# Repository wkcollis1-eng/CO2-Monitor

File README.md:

<div align="center">

# CO2 Monitor

**NDIR CO2 Sensing for Two Rooms, Built to Fail Visibly**

</div>

Two CO2 nodes, one in a bedroom and one in a family room. Each pairs an **Adafruit
SCD30** (PID 4867, a Sensirion NDIR sensor) with a **Seeed XIAO ESP32-C3** on a
small carrier board, inside a **Hammond 1551V4** enclosure. They run **ESPHome**
and report to **Home Assistant**. The bedroom node is built and running; the
family-room node is not built yet.

All behaviour lives in one file, [`esphome/co2-node-common.yaml`](esphome/co2-node-common.yaml).
Each node file holds nothing but its name and its own API key.

*The bedroom node as built: closed on 2026-11-01, and open on 2026-10-27, just
after its USB flash to firmware 1.1 [M: photo EXIF]. More photos are under
[As built](#as-built), and the first five nights of data are under
[Field results](#field-results-the-first-five-nights).*

---

## The problem this is built for

> It is 03:00 in a closed bedroom. The SCD30's cable worked loose an hour ago.
> Nobody is awake to notice, and nobody is coming to fix it tonight.

A CO2 sensor that has stopped answering is dangerous in one specific way: Home
Assistant keeps showing the last good number, and a flat, healthy-looking reading
is exactly what a dead sensor looks like. The acceptance test is **what the node
reports at that moment**, not whether it is online. The firmware is built around
three such moments, named in the header of the common file:

1. **Every boot.** ESPHome 2026.9.1 turns the SCD30's automatic self-calibration
   (ASC) **on** by default and writes that setting to the sensor at every boot
   [S: ESPHome 2026.9.1 source, `scd30/sensor.py:65`, `scd30/scd30.cpp:91`]. ASC
   assumes the sensor regularly sees fresh outdoor air. A closed room in a house
   with no HRV or ERV never does, so ASC would walk the baseline upward where
   nobody would see it. It is turned off explicitly.
2. **Power-up.** The SCD30's first reading after power-up is 0 ppm
   [S: `docs/adafruit-scd30.pdf` p10, p16], and ESPHome passes it through. A
   filter drops it. 0 ppm is not a possible indoor value, so dropping every 0
   costs nothing.
3. **The sensor stops answering.** After 240 s with no reading, the CO2 entity
   goes **unknown** and **CO2 Sensor Fault** turns on. After 900 s the node
   reboots to re-run the sensor setup, **at most three times in a row**. The
   counter survives the reboot, so a dead cable cannot turn into a reboot loop that
   hides it. After the third reboot the node stays up and keeps reporting the fault.
   (1.4: CO2 (2 s) goes unknown at 240 s; CO2, the 1-minute mean, and the SCD30
   temperature and humidity follow at the end of their minute, by 330 s.)

## Status

| | |
|---|---|
| Firmware | **Rev 1.4-draft**, 2026-10-27 (1.0-draft 2026-10-18). On the bedroom node since 2026-10-27 18:13 |
| Compile | Bedroom node, firmware 1.4: compiled on **ESPHome 2026.10.0** with 0 compiler warnings and 0 errors [M: build log, 2026-10-27; config_hash `0x664528e8`]; a deliberately broken lambda fails the same build, so the compile gate can fail. 1.0: both nodes on ESPHome 2026.9.1, 0 warnings, 0 errors [M: build logs, 2026-10-18; config_hash `0xa7e479a5` bedroom, `0xc9ec59d4` family room]. ESPHome's own advisory that an OTA password costs about 3.5 KB of flash prints for both, and is accepted |
| Watchdog | Host-simulated: the clean config passes all 224 checks, and each of the 11 injected faults is caught [M: `harness/faults.py`, 2026-10-27, firmware 1.4; 35 checks and 5 faults on 2026-10-18]. See [The watchdog harness](#the-watchdog-harness) for what that does and does not prove. On the device: SCD30 unplugged on 2026-10-27, firmware 1.1. The node logged the fault at 259 s, HA showed CO2 unknown and the fault on, and the LED strobed [M]. Not repeated on 1.4. The 900 s recovery reboot, and the strobe stopping at the next good reading, have not been seen on the device |
| Deployment | Bedroom node: in Home Assistant since 2026-10-27, firmware 1.4 [M: config_hash `0x664528e8`, ESPHome 2026.10.0, 0 warnings]. On a dresser about 10 ft from the bed [Bill]; 111.65 h with no reset to 2026-11-01 [M]. Family-room node: not built |
| Hardware | **No new PCB.** The carrier is an existing ESP32-C3 sensor-node board. The KiCad file here is that board, unchanged, with the SCD30 and the enclosure placed on it for a 3D fit check |

## Field results: the first five nights

The bedroom node ran from 2026-10-27 18:14 EDT to 2026-11-01 08:52 EST on
firmware 1.4: 111.65 h and five nights [M: InfluxDB and the HA recorder, read
2026-11-01]. That is one node in one room in late October, with outdoor
temperatures from 26.9 to 67 °F [M].

*UBA: 1,000 ppm is the line to open a window, and 2,000 ppm is unacceptable
[S: Umweltbundesamt, "Leitwerte für Kohlendioxid in der Innenraumluft" (2008),
table; not in this repository]. DTU: above 1,150 ppm in a bedroom, sleep quality
is adversely affected [S: DTU news, May 2023, "Ventilate your bedroom at night";
not in this repository].*

### Conclusions

1. **The node is reliable so far, on the healthy path.** It ran 111.65 h with no
   reset and no fault. The three longest gaps in the data were Home Assistant
   restarting, and the node's uptime ran straight through them. This window did
   not exercise the fault path: see Watchdog under [Status](#status).
2. **The room runs elevated, not extreme.** All 6,695 one-minute means were above
   800 ppm, and none reached 1,500 ppm. Four of the five nights averaged above
   1,000 ppm by more than the sensor's ±60 ppm; the fifth, at 1,042 ppm, did not.
   The two highest nights, 1,203 and 1,206 ppm, are 53 to 56 ppm over DTU's 1,150
   line [D]. That is inside ±65 ppm, so this sensor cannot place them above it.
   Nothing here ventilates on its own, so lowering a high reading means opening
   something by hand.
3. **Turning ASC off was right for this room.** The lowest minute in five days was
   874.9 ppm, 449 ppm above the 426 ppm outdoor reference [D: 874.9 − 426]. ASC
   needs regular fresh air, and this room did not reach it once in the window.
4. **CO2 fell on all five mornings, and no single cause covers them.** Oct 30 fell
   with no furnace running, and three other mornings were falling before the usual
   waking hour. See [The furnace](#the-furnace).
5. **No firmware or configuration change follows from this.** The explanations
   below are still models, and a model does not justify changing a running node.

### The node

| Check | Result |
|---|---|
| Resets | 0. Uptime reached 401,944 s with no drop [M] |
| Fault | CO2 Sensor Fault never on, and CO2 Stale Reboots stayed 0 [M: recorder] |
| CO2 (2 s) rows | 198,331 of 200,970 expected, 98.7 % [D: 111.65 h × 1,800 per h]. A lower bound: HA records only changes, so a repeated reading leaves no row |
| Gaps over 4 s | 9. The longest, 218, 137 and 29 s, are HA restarts [M: logbook, Oct 28 22:55, Oct 29 22:04, Oct 31 11:44]. The other six are 13 s or shorter |
| CO2 as a mean | CO2 matches the mean of the previous 60 s of CO2 (2 s): error sd 0.09 ppm, largest 1.08 ppm [D: n = 1,336] |
| Reading noise | 1.04 ppm from one 2 s reading to the next [D: sd of the differences / √2, n = 198,250]. A floor, not the accuracy: neighbouring readings need not be independent |
| WiFi | −30 to −19 dBm, median −21 [M: forward-filled on a 60 s grid, n = 6,700] |
| Free heap | Median by quarter of the run: 203,604, 203,608, 203,568, 203,568 B [M: forward-filled, n = 6,699]. No leak visible over a run this short |
| Loop time | Median 24 ms in every quarter. The 281 ms maximum was at boot [M] |
| SCD30 temperature | 9.54 °F above the upstairs thermostat, sd 0.35 [D: n = 1,219, from 10 h after boot]. Dew points 1.23 °F apart, sd 0.45 [D]. The thermostat is not in the bedroom, so this shows the offset is steady, not how large it is |

### The room

One-minute means, n = 6,695 [M]: 874.9 to 1,313.5 ppm, mean 1,074.2, median
1,075.4. Above 1,000 ppm: 4,597, or 68.7 % [D]. Above 1,150 ppm: 2,042, or 30.5 %
[D]. Above 1,500 ppm: 0.

| Night, 23:00 to 06:00 | n | Mean, ppm | Lowest | Highest | Highest 2 h mean |
|---|---|---|---|---|---|
| Oct 27-28 | 419 | 1,137 | 975 | 1,188 | 1,173 |
| Oct 28-29 | 420 | 1,135 | 1,063 | 1,176 | 1,160 |
| Oct 29-30 | 420 | 1,206 | 1,127 | 1,283 | 1,250 |
| Oct 30-31 | 420 | 1,203 | 1,084 | 1,245 | 1,226 |
| Oct 31-Nov 1 | 480 | 1,042 | 951 | 1,079 | 1,068 |

The last night is 8 h because the clocks went back. The run's highest minute,
1,313.5 ppm, came at 06:37 on Oct 30, just after that night's window closed.

Two adults slept in the room every night, and the door stayed open [Bill]. So
neither head count nor the door explains the 164 ppm between the lowest and highest
night means [D: 1,206 − 1,042].

### The furnace

On four of the five mornings a long furnace cycle started between 05:06 and 05:32,
and CO2 was 95 to 139 ppm lower 15 min after it ended [M]. The fifth morning, Oct 30,
had no cycle: CO2 kept climbing until 06:37 and set the run's highest minute, then
fell 138 ppm by 08:50 with the furnace off [M]. So the morning fall does not need
the furnace. Between 04:00 and 09:00 the fall from peak to low was 155 to 278 ppm on
the four furnace mornings against 138 on Oct 30, and the steepest 10 min was 70 to
173 ppm against 65 [M: window chosen after seeing the data]. One morning without a
cycle is too few to test that difference.

Nobody is usually up before 06:00 [Bill], and that splits the mornings. Oct 30's
peak came after it, so getting up fits that morning. It does not fit three of the
others, which were already falling before 06:00, each with a cycle running [D: 1
min means]:

| Morning | Cycles between 05:00 and 06:00 | CO2 change, 05:00 to 06:00, ppm |
|---|---|---|
| Oct 28 | 05:06-05:31, 05:46-05:58 | −122 |
| Oct 29 | 05:32-05:54 | −77 |
| Oct 30 | None | +33 |
| Oct 31 | 05:31-05:56 | −102 |
| Nov 1 | 05:30-06:22 | +44 |

Nov 1 does not decide it. CO2 rose through the first 26 min of that cycle and fell
from 05:56, on the first morning after the clocks went back, when the usual hour may
have moved on the clock. The waking hour is the usual one, not a log of these
mornings, so this is a pattern and not a proof.

Oct 30 sits inside the longest span without a cycle, 39.07 h from Oct 29 06:58 to
Oct 30 22:02, when CO2 averaged 1,150 ppm [M: n = 2,344].

| Day | CO2 mean, ppm | Furnace cycles | Furnace minutes | Outdoor mean, °F |
|---|---|---|---|---|
| Oct 28 | 1,009 | 9 | 117 | 42.2 |
| Oct 29 | 1,103 | 2 | 51 | 50.7 |
| Oct 30 | 1,191 | 1 | 10 | 55.0 |
| Oct 31 | 1,029 | 6 | 87 | 46.8 |

Across all 25 cycles, CO2 moved by a median of −10.2 ppm in the 25 min from the
start of a cycle, against +3.1 ppm in 196 non-overlapping 25 min windows clear of
the furnace. The difference is −13.3 ppm, one-sided permutation p = 0.0027 [D:
20,000 permutations]. That test does not hold time of day constant, and 10 of the
25 cycles started between 04:00 and 08:00 [M]. Holding it constant weakens the
result: p = 0.027 shuffling within 4 h blocks of the day, and p = 0.054 within 2 h
blocks [D: 20,000 permutations each]. All three treat the windows as independent,
which makes them look stronger than they are. Nor was the fall prompt or uniform: 7
cycles ended the 25 min higher than they began, and the longest, 52.5 min on Nov 1,
was 47 ppm up at 25 min and 95 ppm down 15 min after it ended [M]. The gap shows
before waking, not after: from 04:00 to 06:00 the cycles' median was −31.5 ppm
(n = 6) against +6.1 ppm for the clear windows (n = 10), and from 06:00 to 08:00 it
was −6.6 ppm (n = 4) against −9.2 ppm (n = 8) [D: 2 h blocks, read after seeing the
data, not tested].

So a furnace effect is possible but not shown. Three explanations fit parts of
this [I]: the blower mixes bedroom air with the rest of the house; warm days need
less furnace and also push less air through the house; or people get up at about
the same hour. The blower covers the falls before 06:00 but not Oct 30, and getting
up covers Oct 30 but not those falls, so both may act [I: falsified by a morning
that falls before 06:00 with no cycle running and nobody up]. Four days cannot
separate them, because furnace minutes and outdoor temperature move together. The
family-room node
can test the first: blower mixing
would pull the two rooms together during a cycle [I: falsified if the gap between
them holds through cycles].

### What this does not establish

- **The absolute level.** The only reference is the porch FRC of 2026-10-27, at
  an assumed 426 ppm [I], and nothing has checked the node since: no second
  instrument and no outdoor re-check [M]. If the porch air was above 426 ppm, the
  FRC set the node low, so that error would make these readings too low, not too
  high [I: falsified by a reference meter reading below the node]. Accuracy is
  ±(30 ppm + 3 %) [S: SCD30 Interface Description v1.0-D1, p1], or ±60 ppm at
  1,000 and ±65 ppm at 1,150 [D].
- **The differences between nights.** Head count and the door were the same
  every night, so the 164 ppm has no explanation here.
- **The air at the bed.** The node sits on a dresser about 10 ft from the bed
  [Bill]. These are readings at one point in the room, not in the breathing zone.
- **The rest of the house.** Whether the bedroom is worse than other rooms needs
  the family-room node.
- **Winter.** Five days in late October say nothing about January, when the
  furnace runs far more and the windows stay shut.

## Repository layout

```
esphome/    Node firmware: co2-node-common.yaml plus one thin file per node
harness/    Host-side simulation of the watchdog lambdas, and its fault injector
hardware/   KiCad 10 board (fit-check model) and footprint library
  CO2 Monitor_*.png   The two 3D renders in Fit in the enclosure
  as-built/           Photographs of the bedroom node, and the field-results chart
  3d/                 Vendor 3D models: SCD30, XIAO ESP32-C3, USB-C plug
  adafruit-scd30/     Adafruit's EAGLE files for the SCD30 breakout, with their licence
  Seeed_XIAO_ESP32C3/ KiCad redraw of the XIAO's schematic, for net checking
docs/       Vendor primary sources: Hammond drawing, Sensirion and Adafruit
            SCD30 documents, Seeed XIAO schematic
```

## Hardware

| | |
|---|---|
| Carrier | 23.0 × 38.0 mm, 2-layer, 1.6 mm [M: the board file] |
| MCU | Seeed XIAO ESP32-C3 |
| Sensor | Adafruit SCD30 breakout (PID 4867), I2C address `0x61`. The only device on the bus |
| I2C | SDA GPIO6 (D4), SCL GPIO7 (D5), **50 kHz** [S: `docs/adafruit-scd30.pdf` p15-16] |
| Status LED | GPIO20 (D7), the carrier's green LED. From 1.1 it is the fault light: a 5 Hz strobe on CO2 Sensor Fault, dark otherwise. The vent slots let it show |
| Antenna | Seeed FPC antenna on the XIAO's u.FL socket, marked "XIAO FPC Antenna A-01" [M: photo] |
| Enclosure | Hammond 1551V4, 80 × 80 × 20.3 mm ABS [S: `docs/1551V4BK.pdf`] |

### PH1: sensor header

The SCD30 is cabled from its STEMMA QT socket to PH1, a 1x04 right-angle header.
No header is soldered to the SCD30.

| PH1 pad | Signal | QT wire |
|---|---|---|
| 1 | GND | black |
| 2 | +3V3 | red |
| 3 | SDA | blue |
| 4 | SCL | yellow |

> **Pad 2 is the square pad, not pad 1.** Count from the square pad and you will
> put 3V3 on the wrong wire. Place each wire by colour.

**Feed the breakout from 3V3, never 5 V.** The breakout's 10K SDA and SCL
pull-ups go to VIN [S: `hardware/adafruit-scd30/Adafruit SCD30.brd` netlist], so
VIN sets the high level that the XIAO's 3.3 V pins see on the bus.

### Fit in the enclosure

The 1551V4 is 15.30 mm deep inside, floor to cover [S: Hammond drawing, Section
A-A]. Both boards sit on standoffs on the enclosure floor, not on its bosses.
Figures marked [D] are arithmetic on dimensions measured from the vendor STEP
models:

- **The SCD30 is the tight part.** On 6 mm standoffs it clears the cover by
  0.735 mm nominal [D]. The sensor's height tolerance is ±0.70 mm [S: Sensirion
  SCD30 datasheet, Table 6], and the cover's moulded lettering stands 0.20 mm
  [M: cover STEP], so the worst case is a clash under the lettering. On 5 mm
  standoffs the worst case is 1.035 mm to the cover, or 0.835 mm under the
  lettering [D: 1.035 − 0.20]. On the 3 mm used in the build it is 3.035 mm, or
  2.835 mm under the lettering [D: 1.035 + 2; 3.035 − 0.20].
- **The carrier** on 6 mm standoffs: a XIAO soldered in on pin headers leaves
  0.95 mm [D], and on 3 mm it leaves 3.95 mm [D: 0.95 + 3]. A socketed XIAO does
  not fit on either. The mounting screw under the XIAO has to go in before the
  XIAO does.
- The floor has a 1.0 mm recess at its centre, ±7.53 mm [M: base STEP]. Keep
  standoffs off it.

**As built:** the cover closes over both boards [M: photos below], on 3 mm standoffs
with the XIAO on a 2.5 mm pin header [Bill]. That shows the stack fits. The 3 mm
clearances above are calculated, not measured. The USB cable leaves through a notch at a corner of the vent slots, which
the model does not show.

*KiCad 3D renders of the fit-check model in `hardware/`, not photographs. They do
not record the as-built standoff height, which is the 3 mm above.*

### As built

*Top row: 2026-10-27. Bottom row: 2026-11-01 [M: photo EXIF].*

**Steady green through the slots is not a fault.** It is the breakout's own LED,
and the steady red is the XIAO's, marked CH. Both are lit in the open photos while
the carrier's LED is dark. The carrier's LED is the fault light. It is also green,
but it strobes at 5 Hz.

## Firmware

[`esphome/co2-node-common.yaml`](esphome/co2-node-common.yaml) holds all the
behaviour. [`bedroom-co2-node.yaml`](esphome/bedroom-co2-node.yaml) and
[`family-room-co2-node.yaml`](esphome/family-room-co2-node.yaml) hold only
`substitutions`, their own API encryption key, and the `packages:` include. Both
nodes therefore run the same behaviour from one copy, and a fix made once
reaches both.

### Entities

| Entity | Kind | Notes |
|---|---|---|
| CO2 | sensor, ppm | The 1-minute mean of CO2 (2 s), sent once a minute (1.4; to 1.3, the 60 s reading). **Unknown** at the end of the minute in which CO2 (2 s) goes unknown |
| CO2 (2 s) | sensor, ppm | Every reading, every 2 s. **Unknown** when the sensor has been silent for 240 s. Added in 1.4. Up to 43,200 states a day in the recorder [D: 86,400 / 2]; fewer when readings repeat, since HA records only changes |
| CO2 Sensor Fault | binary_sensor, problem | On from 240 s of silence until the next good reading |
| CO2 Stale Reboots | sensor, diagnostic | Recovery reboots in a row, 0 to 3. Cleared by a good reading |
| Node Status, WiFi Signal, Uptime, Free Heap, Loop Time | diagnostics | |
| Node ESPHome Version, Reset Reason | diagnostics | |
| Node Restart | button | |
| LED Test | button, config | Strobes the LED for 15 s, to prove the LED and that it can be seen. Added in 1.1 |
| Calibration | text, diagnostic | 1.4: `2 s rate; FRC wait (2 min after boot)`, then `2 s rate; FRC ready`, plus the last result; sent only when it changes. (1.2-1.3: `60 s rate`, or the window's `wait` / `ready`.) Added in 1.2 |
| SCD30 Temperature (self-heated), SCD30 Humidity (self-heated) | sensor, diagnostic | The SCD30's own on-board sensor; it reads warm and dry, so it is not the room's T/RH. 1-minute means from 1.4. **Unknown** with CO2 when the sensor is silent. Added in 1.3 |

**The LED is a fault light (1.1, 2026-10-27).** It strobes at 5 Hz while CO2 Sensor
Fault is on, including after a recovery reboot, and is dark the rest of the time.
`harness/led.py` tests the LED lambda both ways, the way `faults.py` tests the watchdog.

**The SCD30 temperature and humidity are diagnostics, not room readings (1.3,
2026-10-27).** The SCD30 heats itself, which skews both readings [S: SCD30
Interface Description v1.0-D1, p15], and the rooms already have their own T/RH
sensors. Firmware 1.0 to 1.2 left them out for that reason. 1.3 adds them
because calibration assumes the sensor is at the temperature of the air it
reads [S: SCD30 Design-In Guidelines D1, p2], and this is the only way to see
that it is.

### Settings that matter

| Setting | Value | Why |
|---|---|---|
| `automatic_self_calibration` | `false` | Moment 1 above |
| `filters: filter_out` | `0.0` | Moment 2 above |
| `altitude_compensation` | `157m` | House elevation about 515 ft [D: 515 × 0.3048 = 156.97 m] |
| `update_interval` | `2s` | 1.4 (was `60s`): the rate FRC is taken at; see below. The watchdog's 240 s is about 120 missed reads |
| `copy` + `throttle_average` | `60s` | 1.4: CO2 is the 1-minute mean of CO2 (2 s); SCD30 temperature and humidity are 1-minute means too |
| `min_version` | `2026.10.0` | The version it was last compiled on. Raise it only after a recompile |

### Calibration: outdoors, by hand

With ASC off, **forced recalibration (FRC) is the only calibration path.**
Sensirion's ±50 ppm lifetime drift figure holds only with ASC or FRC in use
[S: Sensirion SCD30 datasheet v1.0-D1, Table 1, p2; not in this repository].
The node exposes one API action, `forced_recalibration(reference_ppm)`
(1.4; 1.2 and 1.3 also had `frc_prepare`, removed with the 60 s rate):

1. Take the node outdoors, or to an open window in steady air.
2. Leave it powered and reading there for several minutes.
3. Check that Calibration reads `2 s rate; FRC ready`. Sensirion requires a
   2 s measurement rate for at least two minutes before FRC [S: SCD30
   Interface Description v1.0-D1, p14]. From 1.4 the node always measures
   at 2 s, so that holds from 2 min after every boot; before then Calibration
   reads `2 s rate; FRC wait (2 min after boot)`. (1.2-1.3: call `frc_prepare`
   first and wait for its window's `ready`.)
4. At `ready`, and only when the last 3 minutes are flat, call
   `forced_recalibration` with the outdoor reference. The rule used on
   2026-10-27: each minute's sd <= 5 ppm, the 3 minute means within 5 ppm
   of each other, and the 3-min mean no higher than 469 ppm [D: 426 + 43,
   the accuracy at 426 from p1]. There is deliberately no lower bound: a
   plume can only raise outdoor CO2, so a flat reading below 426 is the
   offset FRC exists to remove. The first rule had a lower bound, and it
   rejected a flat window that read about 82 ppm low (R13, CHANGELOG
   2026-10-27). Watch the SCD30 Temperature (1.3) too: the sensor should
   be near the outdoor temperature [S: SCD30 Design-In Guidelines D1, p2].
   The global background was 426.07 ppm in September 2026 [S: NOAA GML,
   Mauna Loa monthly mean, gml.noaa.gov/ccgg/trends, updated 2026-10-09].
   A local outdoor offset above that is [I] and is not used.
5. Calibration then reads `applied N ppm`, or the reason it was not.

Last applied: bedroom node, 2026-10-27 17:01, on the front porch, 426 ppm.
Before it, the 3-min mean was 340.9 ppm; afterwards the reading was 425.7
[M]. It survived the window-end reboot: "PERSIST: PASS (after - before =
-2.0 ppm, limit 43)" [M, 3 readings either side]. That the porch air was
near 426 is [I], falsified by a reference meter there reading near 341.
After 2 of 3 boots that day the first readings started low and climbed
for about 4 min [M]; judge nothing from the first 5 min after a boot.

**Correction, 2026-10-27 17:50 (R13): the cause is the measurement rate,
not the boot.** Each climb began when `frc_prepare` moved the rate from
60 s to 2 s; after the 16:53:57 OTA the 60 s readings held 278, 277 until
`frc_prepare` at 16:55:41 [M]. Each return to 60 s did the reverse,
holding about 4 min and then falling: 340 to 279 after 16:46:26, and 454
to 379 after the 17:15:46 window-end reboot [M]. In the same air the 60 s
reading sat 60 to 70 ppm below the 2 s reading [D: 338.5 - 278, 343.0 -
277, 448.9 - 381; n = 3 transitions, one unit, one afternoon]. The
mechanism is unknown. FRC is taken at 2 s, as p14 asks, and the node runs
at 60 s, so its readings likely sit about 65 ppm below the reference [I:
falsified by the node, outdoors at 60 s and settled, reading near 426].
The PERSIST figure compared 2 s readings with 60 s readings that had not
fallen yet: it shows the calibration was not lost (at 60 s, 277 before
the FRC and 379 after it [M]), not that it is accurate. Judge nothing for
10 min after a change of rate.

**The remedy, firmware 1.4 (2026-10-27, Bill: "measure every 2 s all the
time and send HA a 1-minute average and show both on the graphs").** The
node now always measures at 2 s, the rate the FRC was taken at. Before the
OTA the bedroom read 921 ppm at 60 s, falling about 1 ppm/min [M: n = 12,
18:01-18:13]. The 2 s rate started with the 18:13:23 boot. About 2 min
later CO2 (2 s) read 1005 to 1010 [M: n = 9, 18:15], a step of about +86 ppm
[D: 1007.4 - 921.4]. The 1-minute means were 931.1, 995.4, 1006.5 and 999.4
[M: 18:14:24 to 18:17:24]; the first one held the climb, as the earlier
switches did. The settled means are +78 to +85 [D: 999.4 - 921.4; 1006.5 -
921.4]. The prediction, stated before the OTA, was +60 to 70 [I]. The
direction held and the step came out larger. One switch, one room, one
evening; who was in the room was not recorded.

(1.2-1.3) The window ends with a reboot 20 min after `frc_prepare`. Setup writes the
60 s rate back, because the SCD30 keeps its interval in non-volatile memory
[S: same document, p9]; a forgotten window cannot leave it at 2 s.
From 1.4, setup writes 2 s at every boot in the same way.

The node refuses a call before `ready` (1.4: in the first 2 min after a
boot), or a reference outside 400 to
2000 ppm, and Calibration shows the refusal. The time check runs first,
so a test call with 399 can never apply.
**Never call it from an automation.** A reference given indoors bakes the
room's excess CO2 into every later reading.

### The watchdog

A 30 s interval measures the age of the last good reading. It uses unsigned
arithmetic, so it survives the 49-day `millis()` wrap.

| Age of last reading | Action |
|---|---|
| 240 s | CO2 goes unknown, CO2 Sensor Fault turns on, a warning is logged |
| 900 s | Recovery reboot, if fewer than 3 in a row so far. The count is stored in flash, so it survives the reboot |
| after the 3rd reboot | No more reboots. The node stays online, reporting the fault |

A recovery boot starts with the fault still on, so Home Assistant never sees a
"healthy" gap between reboots. The first good reading clears the fault and the
count. Why 240 s: four missed 60 s reads always raise the fault, and three can,
if a 30 s tick lands just before the fourth read is due. After boot, the dropped 0 ppm reading comes
at about 60 s and the first real one at about 120 s, which leaves about 120 s of
margin [I: falsified if a boot with a working sensor logs "no SCD30 reading"].
1.4: at 2 s, 240 s is about 120 missed reads, and the first real reading comes
at about 4 s, so the boot margin is about 236 s [I: same falsifier]. CO2 (2 s)
goes unknown at 240 s; the 1-minute means (CO2, temperature, humidity) go
unknown at the end of the minute that holds no number, by 330 s [M: harness S2].

### Building

1. Copy the three files in `esphome/` into your ESPHome config directory.
2. Provide a `secrets.yaml` with these keys: `wifi_ssid`, `wifi_password`,
   `ap_password`, `ota_password`, `api_key_bedroom_co2_node`,
   `api_key_family_room_co2_node`.
3. Compile with ESPHome 2026.10.0 or later (the `min_version`; 1.4 was built on it). Do the first flash over USB, then
   use OTA. Logging runs over the C3's native USB Serial/JTAG, which frees GPIO20
   for the LED.

Neither node file sets `wifi: use_address` yet. Add your DHCP reservation there
if your ESPHome host cannot resolve `.local` names.

## The watchdog harness

`harness/` runs the watchdog's real lambdas on a PC, against simulated time.

- [`gen.py`](harness/gen.py) extracts the `on_boot`, `on_value` and `interval`
  lambdas **verbatim** from `co2-node-common.yaml`, and wraps them in
  [`sim.cpp.in`](harness/sim.cpp.in). The lambda text is never retyped, so the
  test runs exactly what the firmware runs.
- `sim.cpp.in` stubs `millis()` (including the 32-bit wrap), the restored
  globals, `App.safe_reboot()`, the entities and (1.4) `throttle_average`, as
  ESPHome 2026.10.0's `filter.cpp` implements it. It runs eight scenarios: healthy,
  swept over boot, tick and averaging phases;
  a late first read at about 303 s; a sensor that dies and never returns; one
  that dies and returns at 50 min; a 100 s glitch; a 600 s glitch that recovers;
  healthy across the `millis()` wrap, swept over the tick phase in 500 ms steps;
  and dead from power-up.
- [`faults.py`](harness/faults.py) proves the test can fail. It runs the clean
  config, which must PASS, then eleven single-span faults, each of which must FAIL:
  the NaN guard removed, the reboot cap raised to 4, the stale threshold cut to
  24 s, wrap-unsafe age arithmetic, a recovery boot that clears the fault, and
  (1.3) a stale SCD30 temperature or humidity left showing, or blanked while
  healthy; (1.4) a stale CO2 left showing, the NaN sent to the mean instead of
  the 2 s reading, or the 2 s reading blanked while healthy.

```
pip install ziglang pyyaml
python harness/faults.py esphome/co2-node-common.yaml harness/work
```

The last line should read `FAULTS: PASS (0 of 12 directions wrong)` [M, 2026-10-27,
firmware 1.4; the clean config `RESULT: PASS (224 checks)`]. Toolchain last recorded as Python 3.14.3, ziglang 0.16.0 and
PyYAML 6.0.3 [M, 2026-10-18].

**What the harness does not prove:** anything about the SCD30 driver, the I2C
bus, or ESPHome's own flash storage. It shows that the lambdas, given the stubbed
behaviour, do what this README says. The stub for `safe_reboot()` persisting the
reboot count was taken from ESPHome 2026.9.1's shutdown order, where the globals
store themselves before the preferences flush. A different ESPHome version needs
that re-read.

## Working on the board

Open `hardware/CO2 Monitor.kicad_pro` in **KiCad 10**. The in-repo 3D models
resolve through `${KIPRJMOD}`, so a fresh clone renders the assembly without any
path fixing.

**This is a fit-check model, not a board to fabricate.** Its tracks, vias,
outline, and footprint placement and pads are identical to the carrier board's
own file [M: 69 tracks and vias, 8 outline items and 10 footprints compared,
2026-10-18]. The Hammond base and cover models hang on the SCD30 footprint.

Know these before you file a bug against it:

1. **The design rules belong to another board.** `CO2 Monitor.kicad_pro`
   carries a minimum clearance of 0.2032 mm and a copper-to-edge clearance of
   0.025 mm, inherited from an unrelated cap-touch board. The carrier's own
   rules are not in this repository. Set the rules yourself before any revision.
2. **`kicad-cli pcb drc` reports 16 to 18 findings, and the count varies from
   run to run on an unchanged file** [M: 6 runs, 2026-10-18]:

   | n | severity | rule | cause |
   |---|---|---|---|
   | 7 to 9 | error | `clearance` | 0.2000 mm SCL/SDA gaps against the inherited 0.2032 mm minimum. KiCad reports a different selection of track pairs on each run, always among the same 11 tracks |
   | 4 | warning | `lib_footprint_mismatch` | C1, LED, PH1, R1 differ from their library versions |
   | 4 | warning | `silk_edge_clearance` | cosmetic |
   | 1 | warning | `lib_footprint_issues` | U1: library `UPS_Custom` is not in this project's library table |

   Compare DRC results by the objects they name, not by the count.
3. **7 model references do not resolve:** 5 hidden ones, and 2 visible
   duplicates of the XIAO that point at files not in this repository. The XIAO
   renders from `3d/`, once.
4. **The footprint library's own 3D paths are broken.** The `.kicad_mod` files in
   `CO2_Monitor/CO2_Monitor.pretty/` point at paths that do not exist relative to
   this project. The board stores its footprints inline, and those copies are the
   ones that render, so this matters only if you re-place a footprint from the
   library. The library is also not registered in a `fp-lib-table`.

## Third-party assets

Full detail, including the terms for each file, is in
**[THIRD_PARTY_NOTICES.md](THIRD_PARTY_NOTICES.md)**. These files are *not*
covered by this repository's own licences.

| Asset | Origin | Terms |
|---|---|---|
| `hardware/3d/4867 Adafruit SCD30.step` | Adafruit, `Adafruit_CAD_Parts` | MIT |
| `hardware/adafruit-scd30/` | Adafruit, `Adafruit-SCD-30-PCB` | CC BY-SA 3.0 |
| `hardware/3d/seeed-studio-xiao-esp32-c3.step` | Seeed Studio | vendor file |
| `hardware/CO2_Monitor/CO2_Monitor.3dshapes/` | Hammond, split into base and cover | vendor file, modified |
| `hardware/3d/usb-c-…snapshot.1/` | GrabCAD community model | **author and licence not recovered**; delete it if that matters to you. It also appears in the two renders |
| `docs/*.pdf` | Hammond, Seeed, Sensirion, Adafruit | publisher's copyright |

## Credentials

Every credential resolves through ESPHome `!secret`. No `secrets.yaml` is
committed, and the repository's `.gitignore` excludes one. Each commit is
scanned by gitleaks at commit time, and the full history was scanned before
publication, with this repository's own rules. Those rules extend the defaults
to catch inline Wi-Fi and OTA credentials.

---

## License

Three licences, because this repository holds three different kinds of work:

| Content | Paths | Licence |
|---|---|---|
| Hardware design | `hardware/` | [CERN-OHL-S v2](LICENSE-HARDWARE) |
| Code | `esphome/`, `harness/` | [MIT](LICENSE-CODE) |
| Documentation | this README | [CC BY 4.0](https://creativecommons.org/licenses/by/4.0/) |

See **[LICENSE](LICENSE)** for the full breakdown and attribution examples, and
**[THIRD_PARTY_NOTICES.md](THIRD_PARTY_NOTICES.md)** for the vendor files that
none of the above covers.

```
Copyright (C) 2026 William K. Collis

This source describes Open Hardware and is licensed under the CERN-OHL-S v2.

You may redistribute and modify this source and make products using it under
the terms of the CERN-OHL-S v2 (https://ohwr.org/cern_ohl_s_v2.txt).

This source is distributed WITHOUT ANY EXPRESS OR IMPLIED WARRANTY, INCLUDING
OF MERCHANTABILITY, SATISFACTORY QUALITY AND FITNESS FOR A PARTICULAR PURPOSE.
Please see the CERN-OHL-S v2 for applicable conditions.

Source location: https://github.com/wkcollis1-eng/CO2-Monitor
```

---

## 💝 Support This Project

If the watchdog design or its harness saved you time on your own sensor node,
sponsorship funds continued instrumentation, hardware and documentation.

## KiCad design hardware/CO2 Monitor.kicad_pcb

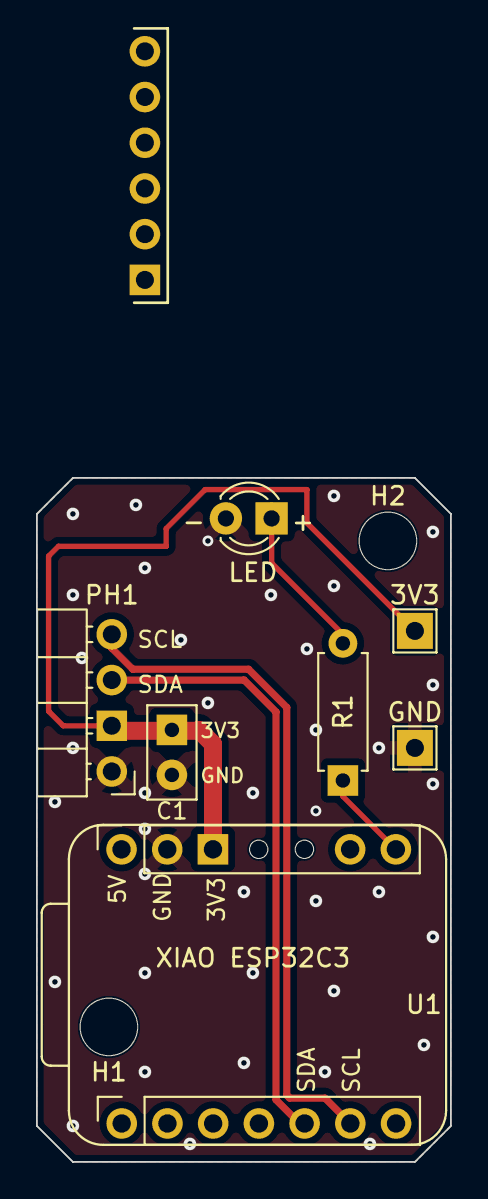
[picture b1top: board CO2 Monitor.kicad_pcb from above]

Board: 2 copper layers, 23.0 x 38.0 mm, 9 parts (0 on the bottom side), 6 nets.

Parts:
3V3: TestPoint_THTPad_2.0x2.0mm_Drill1.0mm
C1: .1uF 50V; C_Disc_D5.0mm_W2.5mm_P2.50mm
GND: TestPoint_THTPad_2.0x2.0mm_Drill1.0mm
H1, H2: M3; MountingHole_3.2mm_M3
LED: Green; LED_D3.0mm
PH1: PinHeader_1x04_P2.54mm_Horizontal
R1: 1K Ohm; R_Axial_DIN0207_L6.3mm_D2.5mm_P7.62mm_Horizontal
U1: Xiao ESP32C3; XIAO ESP32C3

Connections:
+3V3: 3V3.1, C1.2, PH1.2, U1.3V3
GND: C1.1, GND.1, LED.1, PH1.1, U1.GND
GPIO20LED: R1.1, U1.GPIO20
LED: LED.2, R1.2
SCL: PH1.4, U1.SCL
SDA: PH1.3, U1.SDA

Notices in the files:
README.md:
Docs: CC BY 4.0
